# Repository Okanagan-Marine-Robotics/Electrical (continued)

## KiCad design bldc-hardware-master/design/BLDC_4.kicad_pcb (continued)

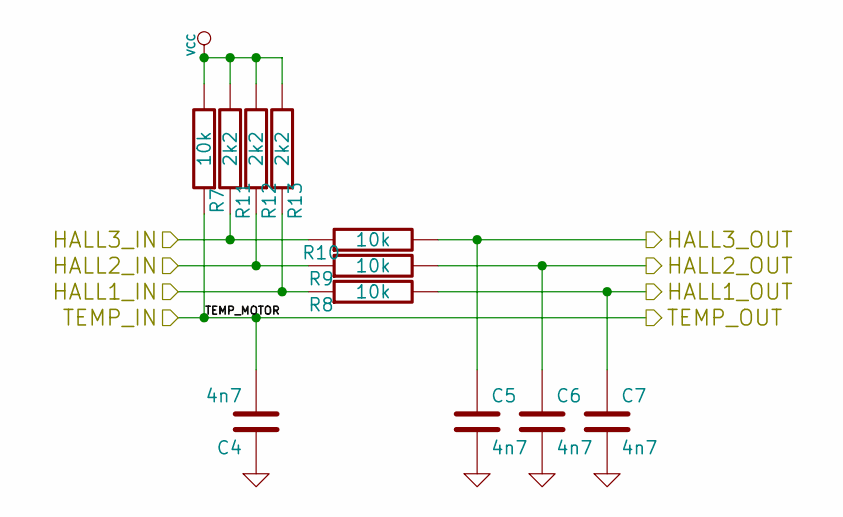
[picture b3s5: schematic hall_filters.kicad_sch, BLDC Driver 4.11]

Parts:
C4, C5, C6, C7: 4n7; SMD-0603_c
R7, R8, R9, R10: 10k; SMD-0603_r
R11, R12, R13: 2k2; SMD-0603_r

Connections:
/Filters/HALL1_IN: R8.1, R13.1; also elsewhere on the board
/Filters/HALL1_OUT: C7.1, R8.2; also elsewhere on the board
/Filters/HALL2_IN: R9.1, R12.1; also elsewhere on the board
/Filters/HALL2_OUT: C6.1, R9.2; also elsewhere on the board
/Filters/HALL3_IN: R10.1, R11.1; also elsewhere on the board
/Filters/HALL3_OUT: C5.1, R10.2; also elsewhere on the board
/Filters/TEMP_MOTOR: C4.2, R7.1; also elsewhere on the board
GND: C4.1, C5.2, C6.2, C7.2; also elsewhere on the board
VCC: R7.2, R11.2, R12.2, R13.2; also elsewhere on the board

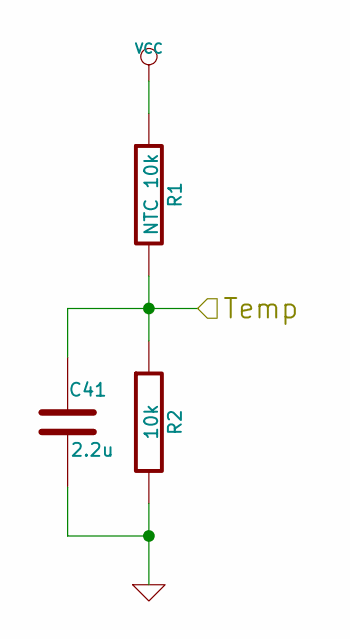
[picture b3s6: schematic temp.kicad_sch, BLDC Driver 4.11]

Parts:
C41: 2.2u; SMD-0603_c
R1: NTC 10k; SMD-0603_r
R2: 10k; SMD-0603_r

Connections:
/MCU/ADC_TEMP: C41.1, R1.2, R2.1; also elsewhere on the board
GND: C41.2, R2.2; also elsewhere on the board
VCC: R1.1; also elsewhere on the board

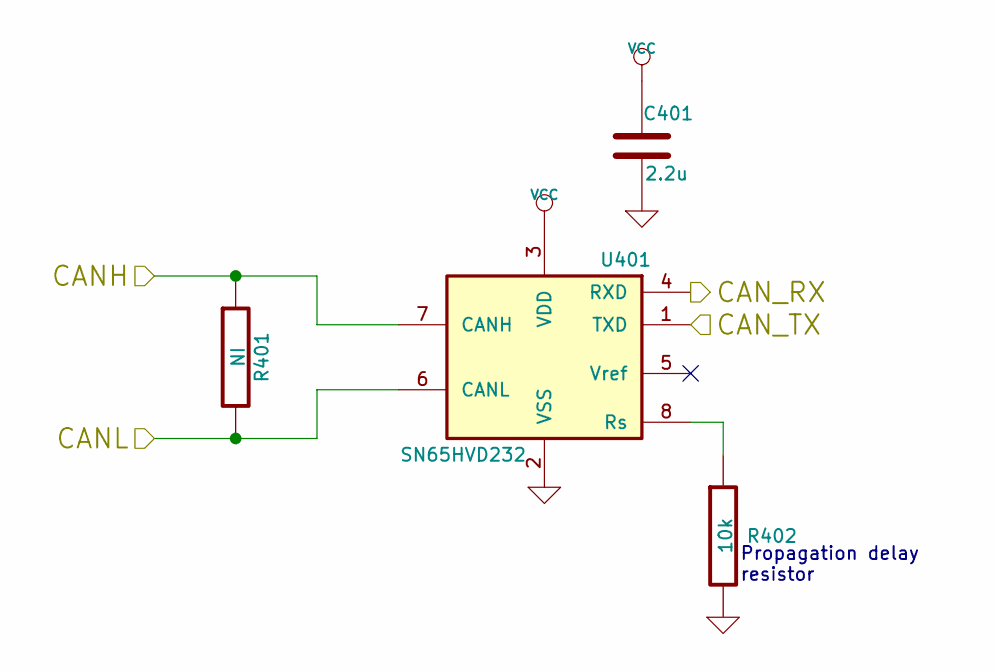
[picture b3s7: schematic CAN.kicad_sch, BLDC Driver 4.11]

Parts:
C401: 2.2u; SMD-0603_c
R401: NI; SMD-0603_r
R402: 10k; SMD-0603_r
U401: SN65HVD232; SOIC-8-W

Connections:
/CAN bus transceiver/CANH: R401.1, U401.7 (CANH); also elsewhere on the board
/CAN bus transceiver/CANL: R401.2, U401.6 (CANL); also elsewhere on the board
/CAN bus transceiver/CAN_RX: U401.4 (RXD); also elsewhere on the board
/CAN bus transceiver/CAN_TX: U401.1 (TXD); also elsewhere on the board
GND: C401.2, R402.2, U401.2 (VSS); also elsewhere on the board
unnamed: R402.1, U401.8 (Rs)
VCC: C401.1, U401.3 (VDD); also elsewhere on the board

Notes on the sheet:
Propagation delay resistor

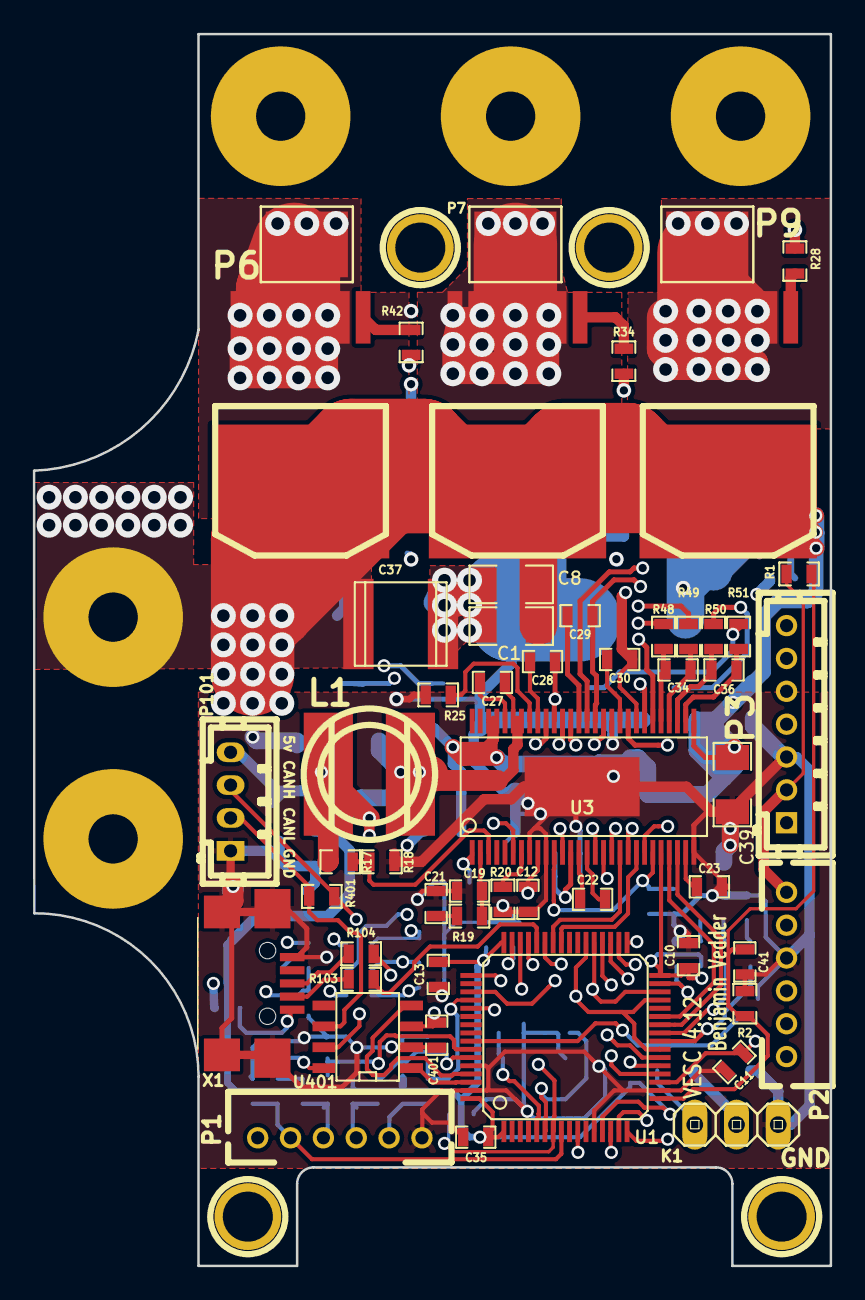
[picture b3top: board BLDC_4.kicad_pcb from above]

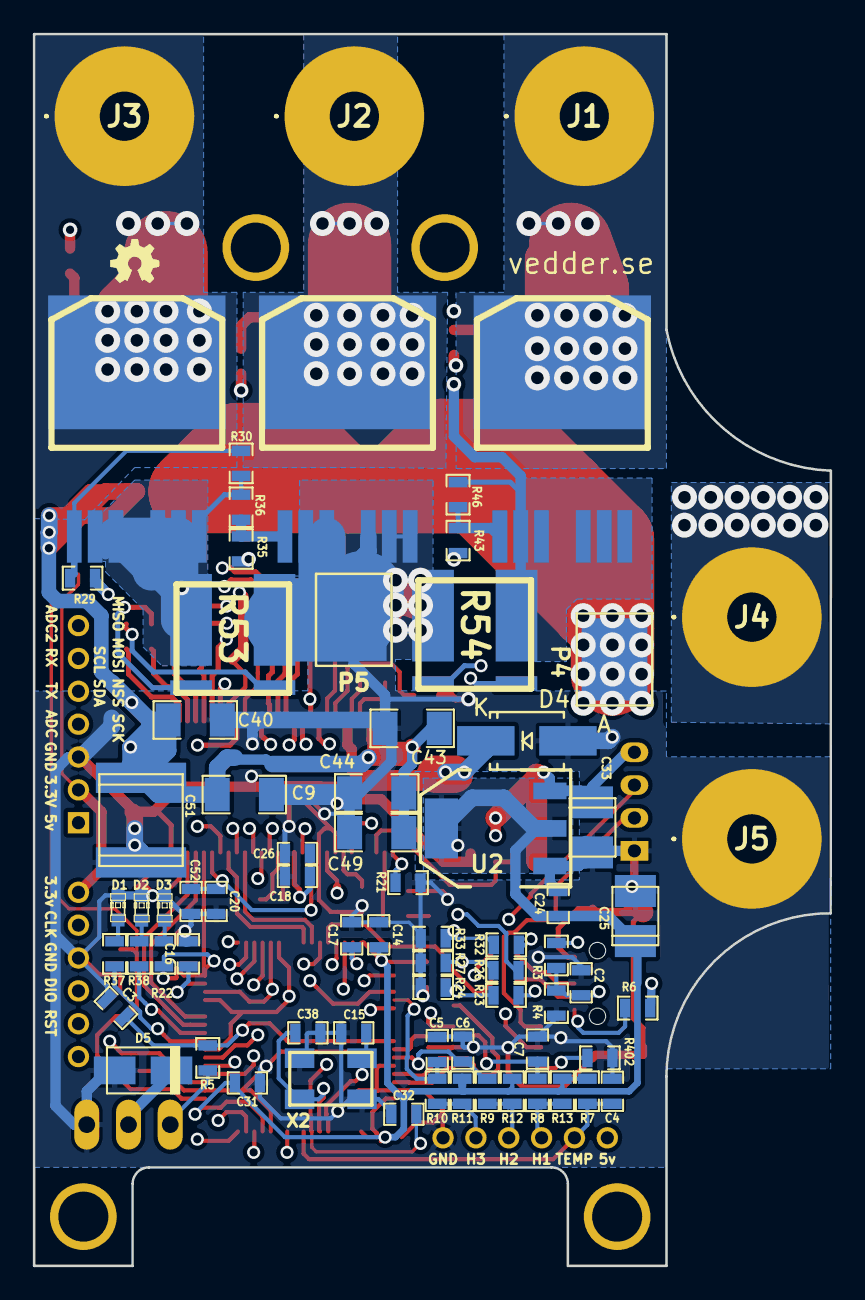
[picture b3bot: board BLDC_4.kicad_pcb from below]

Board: 4 copper layers, 48.5 x 75.0 mm, 131 parts (73 on the bottom side), 96 nets.

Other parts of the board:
1PIN, 1PIN#2, 1PIN#3, 1PIN#4: P***; 1pin

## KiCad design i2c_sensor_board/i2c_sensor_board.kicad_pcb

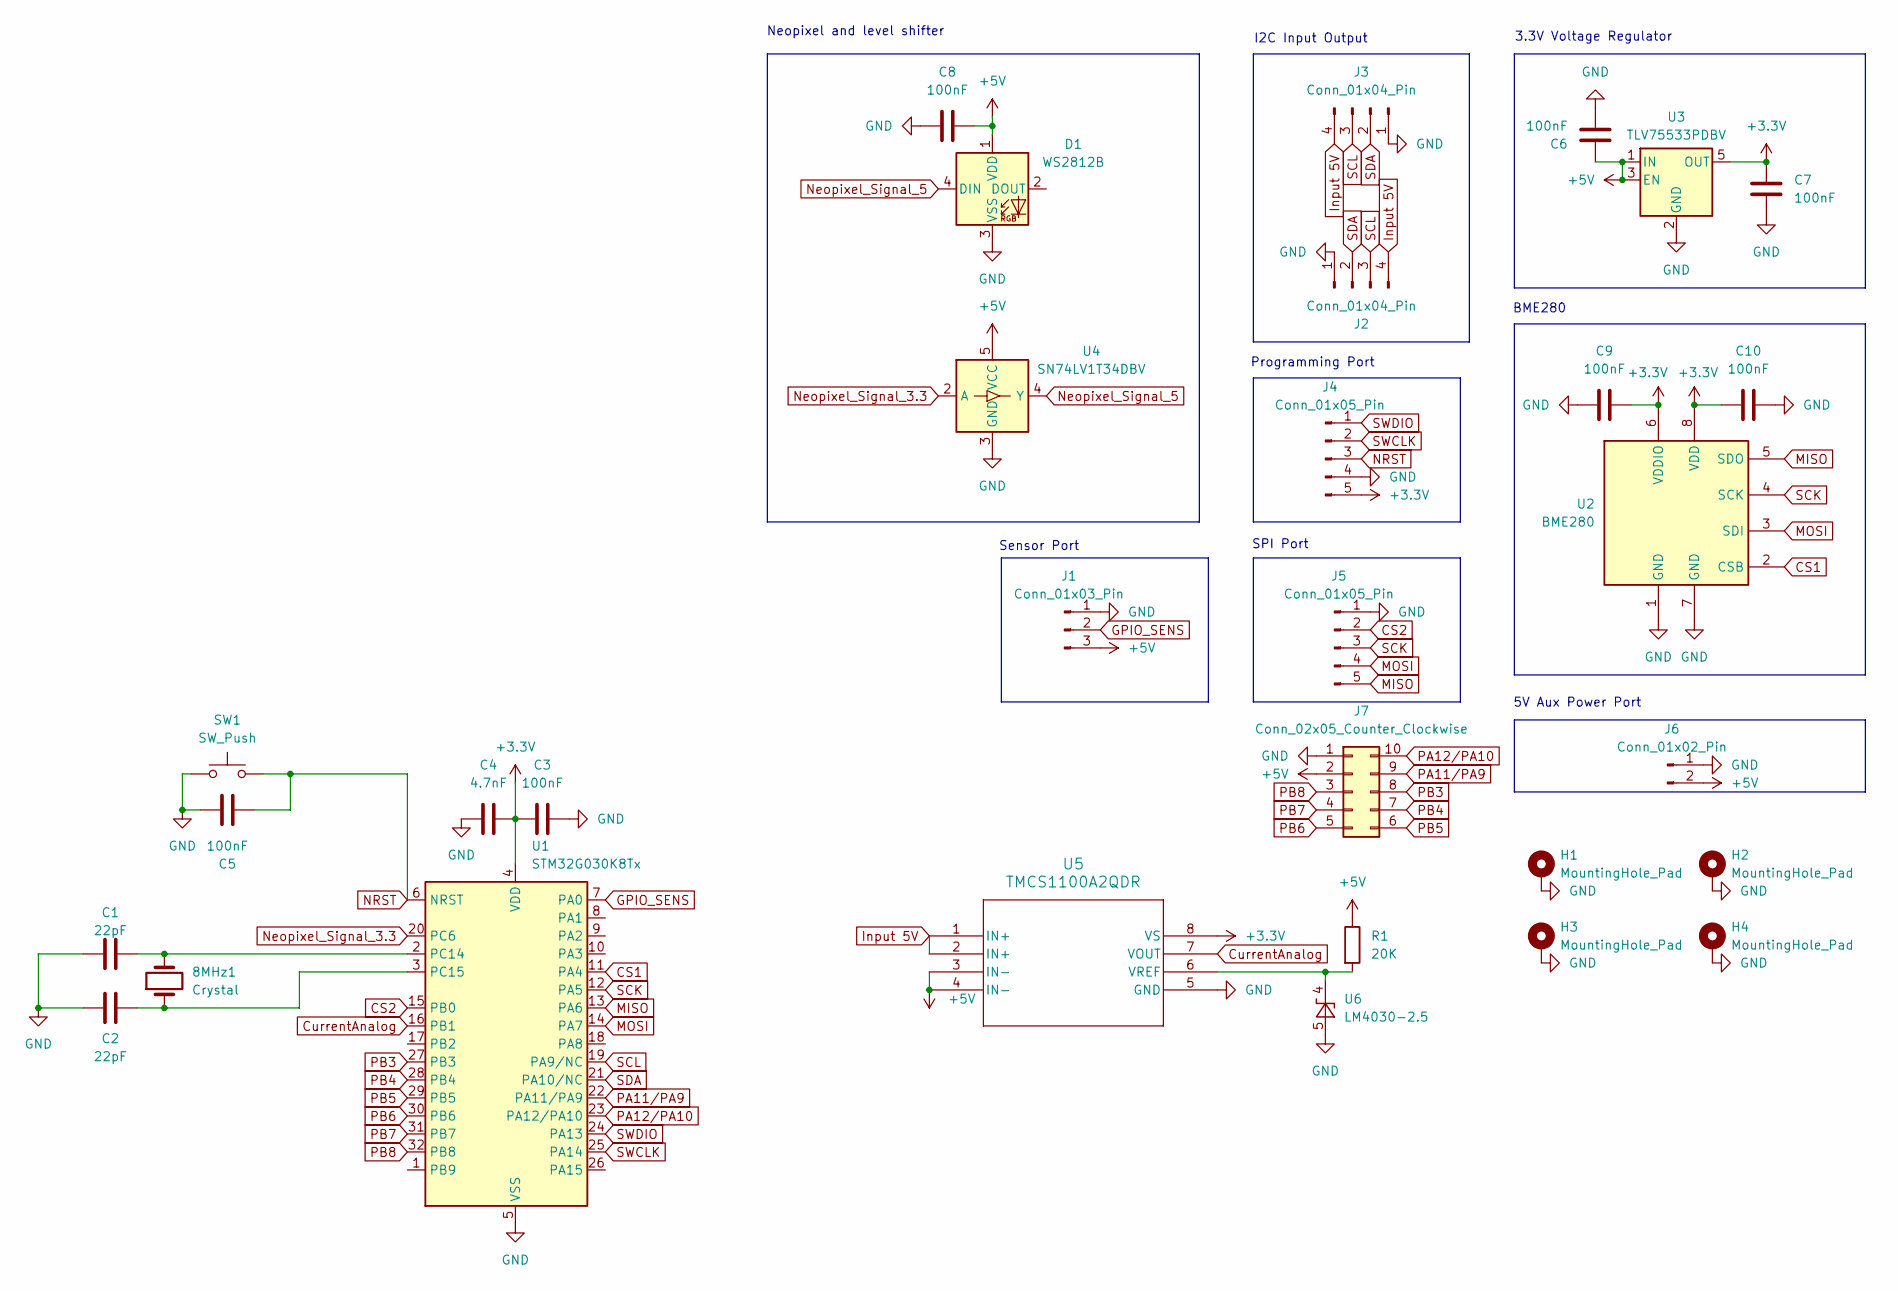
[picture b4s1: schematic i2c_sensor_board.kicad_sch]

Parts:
8MHz1: Crystal; Crystal_HC49-U_Vertical
C1, C2: 22pF; C_0603_1608Metric_Pad1.08x0.95mm_HandSolder
C3, C5, C6, C7, C8, C9, C10: 100nF; C_0603_1608Metric_Pad1.08x0.95mm_HandSolder
C4: 4.7nF; C_0603_1608Metric_Pad1.08x0.95mm_HandSolder
D1: WS2812B; LED_WS2812B_PLCC4_5.0x5.0mm_P3.2mm
H1, H2, H3, H4: MountingHole_Pad; MountingHole_3.2mm_M3_DIN965_Pad
J1: Conn_01x03_Pin; JST_XH_B3B-XH-AM_1x03_P2.50mm_Vertical
J2, J3: Conn_01x04_Pin; JST_XH_B4B-XH-AM_1x04_P2.50mm_Vertical
J4: Conn_01x05_Pin; PinSocket_1x05_P2.54mm_Vertical
J5: Conn_01x05_Pin; JST_XH_B5B-XH-AM_1x05_P2.50mm_Vertical
J6: Conn_01x02_Pin; JST_XH_B2B-XH-AM_1x02_P2.50mm_Vertical
J7: Conn_02x05_Counter_Clockwise; PinHeader_2x05_P2.54mm_Vertical
R1: 20K; R_0603_1608Metric_Pad0.98x0.95mm_HandSolder
SW1: SW_Push; SW_SPST_PTS810
U1: STM32G030K8Tx; LQFP-32_7x7mm_P0.8mm
U2: BME280; Bosch_LGA-8_2.5x2.5mm_P0.65mm_ClockwisePinNumbering
U3: TLV75533PDBV; SOT-23-5
U4: SN74LV1T34DBV; SOT-23-5
U5: TMCS1100A2QDR; SOIC8_D_TEX
U6: LM4030-2.5; SOT-23-5

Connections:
+3.3V: C3.1, C4.2, C7.1, C9.1, C10.2, J4.5, U1.4 (VDD), U2.6 (VDDIO), U2.8 (VDD), U3.5 (OUT), U5.8 (VS)
+5V: C6.1, C8.2, D1.1 (VDD), J1.3, J6.2, J7.2, R1.1, U3.1 (IN), U3.3 (EN), U4.5 (VCC), U5.3 (IN-), U5.4 (IN-)
CS1: U1.11 (PA4), U2.2 (CSB)
CS2: J5.2, U1.15 (PB0)
CurrentAnalog: U1.16 (PB1), U5.7 (VOUT)
GND: C1.1, C2.1, C3.2, C4.1, C5.1, C6.2, C7.2, C8.1, C9.2, C10.1, D1.3 (VSS), H1.1, H2.1, H3.1, H4.1, J1.1, J2.1, J3.1, J4.4, J5.1, J6.1, J7.1, SW1.1, U1.5 (VSS), U2.1 (GND), U2.7 (GND), U3.2 (GND), U4.3 (GND), U5.5 (GND), U6.5 (A)
GPIO_SENS: J1.2, U1.7 (PA0)
Input 5V: J2.4, J3.4, U5.1 (IN+), U5.2 (IN+)
MISO: J5.5, U1.13 (PA6), U2.5 (SDO)
MOSI: J5.4, U1.14 (PA7), U2.3 (SDI)
NRST: C5.2, J4.3, SW1.2, U1.6 (NRST)
Neopixel_Signal_3.3: U1.20 (PC6), U4.2 (A)
Neopixel_Signal_5: D1.4 (DIN), U4.4 (Y)
unnamed: 8MHz1.2, C1.2, U1.2 (PC14)
unnamed: 8MHz1.1, C2.2, U1.3 (PC15)
unnamed: R1.2, U5.6 (VREF), U6.4 (K)
PA11/PA9: J7.9, U1.22 (PA11/PA9)
PA12/PA10: J7.10, U1.23 (PA12/PA10)
PB3: J7.8, U1.27 (PB3)
PB4: J7.7, U1.28 (PB4)
PB5: J7.6, U1.29 (PB5)
PB6: J7.5, U1.30 (PB6)
PB7: J7.4, U1.31 (PB7)
PB8: J7.3, U1.32 (PB8)
SCK: J5.3, U1.12 (PA5), U2.4 (SCK)
SCL: J2.3, J3.3, U1.19 (PA9/NC)
SDA: J2.2, J3.2, U1.21 (PA10/NC)
SWCLK: J4.2, U1.25 (PA14)
SWDIO: J4.1, U1.24 (PA13)

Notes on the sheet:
Programming Port
Sensor Port
Neopixel and level shifter
5V Aux Power Port
I2C Input Output
SPI Port
3.3V Voltage Regulator
BME280

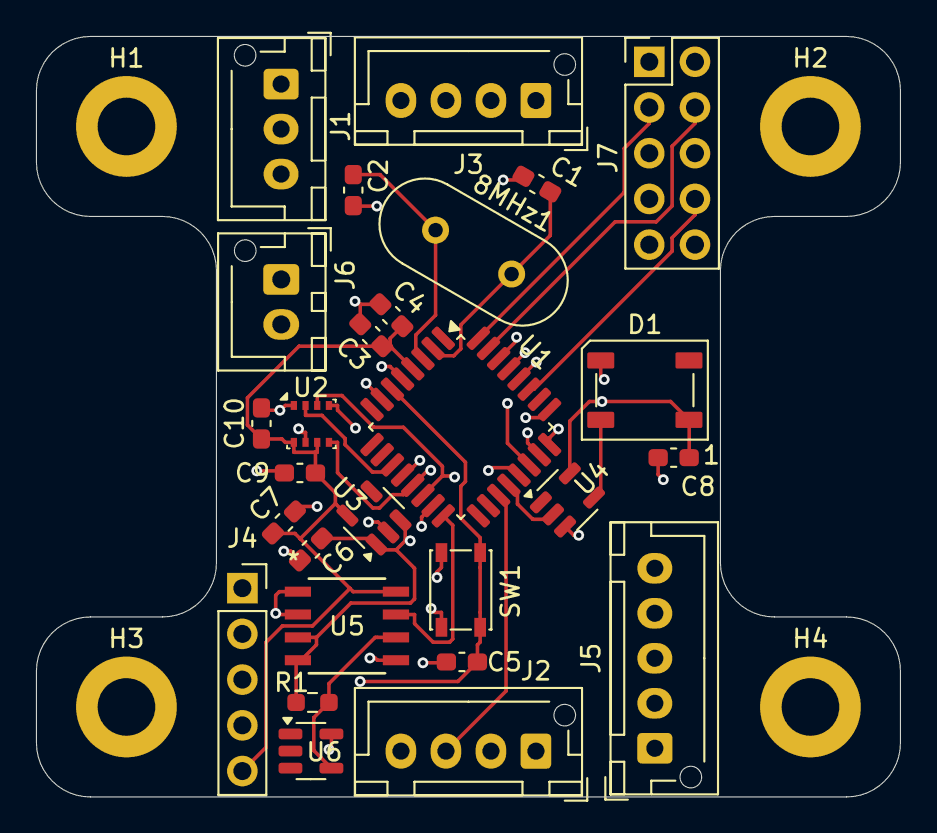
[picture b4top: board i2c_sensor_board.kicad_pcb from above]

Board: 6 copper layers, 48.0 x 42.2 mm, 31 parts (0 on the bottom side), 29 nets.

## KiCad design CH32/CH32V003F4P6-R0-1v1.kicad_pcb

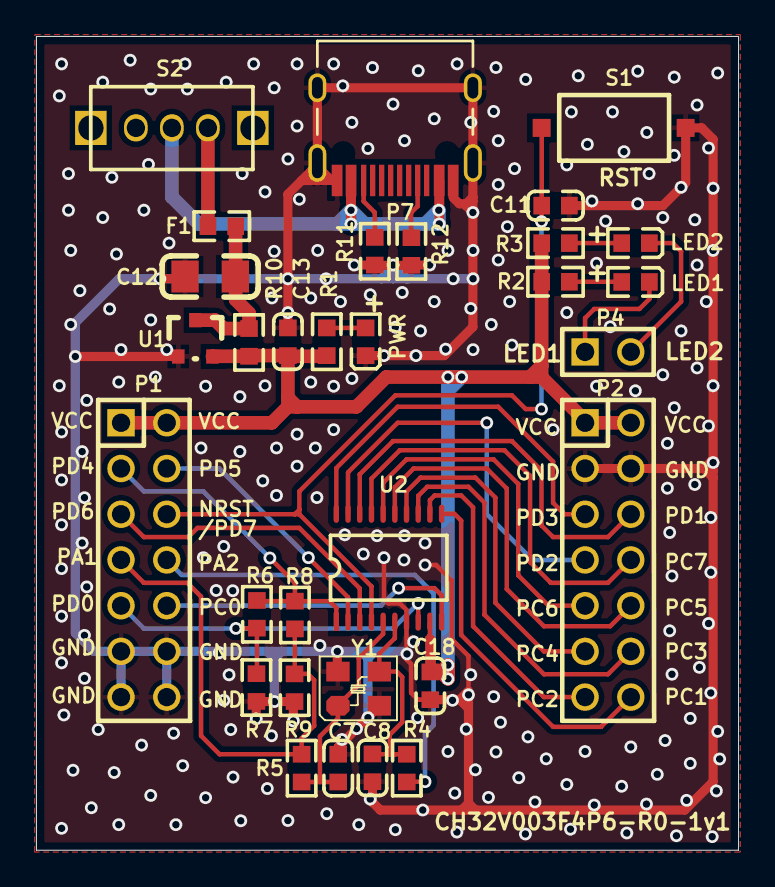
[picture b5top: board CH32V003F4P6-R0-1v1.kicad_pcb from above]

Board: 2 copper layers, 39.0 x 45.2 mm, 31 parts (0 on the bottom side), 32 nets.

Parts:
C7, C8: 22pF; 0603_C
C11, C18: 0.1uF; 0603_C
C12: 10uF; 3216_C
C13: 2.2uF; 0603_C
F1: 500mA; 0603
LED1: LED1 blue; 0603+
LED2: LED2 blue; 0603+
P1, P2: Header 7X2; IDC14-2.54mm
P4: HEADER 2; SIP2-2.54mm
P7: TYPE-C; TYPE-C-Receptacle-2.0
PWR: POWER red; 0603+
R1, R2, R3: 1K; 0603
R4, R5, R6, R7, R8, R9, R10, R11, R12: 0R; 0603
S1: NRST; SMD_6.1x3.65x2.5mm-KEY
S2: SW; SW1
U1: 6219P33M; SOT-23
U2: CH32V003F4P6; TSSOP20
Y1: 24MHz; XT3225

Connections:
+5V: P7.A4, P7.B4, S2.1
GND: C7.1, C8.1, C11.1, C12.2, C13.1, C18.1, P1.11, P1.12, P1.13, P1.14, P2.3, P2.4, P7.0, P7.A1, P7.B1, PWR.2, R7.2, R9.2, R11.2, R12.2, S1.2, U1.1, U2.7, Y1.2, Y1.4
LED1: LED1.2, P4.1
LED2: LED2.2, P4.2
NRST: C11.2, P1.6, S1.1, U2.4
NetC12_1: C12.1, F1.2, R10.1, U1.3
NetF1_1: F1.1, S2.3
NetLED1_1: LED1.1, R2.2
NetLED2_1: LED2.1, R3.2
NetP7_A5: P7.A5, R12.1
NetP7_B5: P7.B5, R11.1
NetPWR_1: PWR.1, R1.1
PA1: P1.7, R5.2, R8.2, R9.1
PA2: P1.8, R4.2
PC0: P1.10, U2.10
PC1: P2.14, U2.11
PC2: P2.13, U2.12
PC3: P2.12, U2.13
PC4: P2.11, U2.14
PC5: P2.10, U2.15
PC6: P2.9, U2.16
PC7: P2.8, U2.17
PD0: P1.9, R6.2, R7.1, U2.8
PD1: P2.6, U2.18
PD2: P2.7, U2.19
PD3: P2.5, U2.20
PD4: P1.3, R6.1, R8.1, U2.1
PD5: P1.4, U2.2
PD6: P1.5, U2.3
VCC: C13.2, C18.2, P1.1, P1.2, P2.1, P2.2, R1.2, R2.1, R3.1, R10.2, U1.2, U2.9
XI: C7.2, R5.1, U2.5, Y1.1
XO: C8.2, R4.1, U2.6, Y1.3

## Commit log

2024-09-11 esp mobo kicad project
2024-09-14 add submodule for testing
2024-09-15 Test
2024-09-15 Test2
2024-09-15 OP Amp layout added
2024-09-16 Compressed Layout
2024-09-16 New Layout
2024-09-29 Update ESC Mobo with OptoCOuplers and improved circuit
2024-10-01 Update ESC Mobo with comments and input protection as well as motor i2c
2024-10-05 Added schematic for CH32
2024-10-11 Update ESC Mobo
2024-10-14 Update ESC Mobo with BME280
2024-10-15 Update ESC Mobo with board
2024-10-19 Update ESC Mobo Silkscreen
2024-10-19 Update ESC Mobo Ground Points
2024-10-19 Update ESC Mobo Ground Connectors
2024-10-20 Add I2C boards
2024-11-15 Added VESC KiCad Files
2024-11-15 added libs
2024-11-15 saving progress
2024-11-15 more changes
2024-11-15 changees
2024-11-23 added 3D Models
2024-11-23 Lots of changes
2024-11-23 Merge
2024-11-23 small changes
2024-12-02 adding current motor_controller esp32 code
2025-03-03 Updated motor_control.ino
2025-03-29 Groovy stuff soon to be replaced by Yattin
2025-03-31 Remove Hydrophones
2025-03-31 Add leak sensor
